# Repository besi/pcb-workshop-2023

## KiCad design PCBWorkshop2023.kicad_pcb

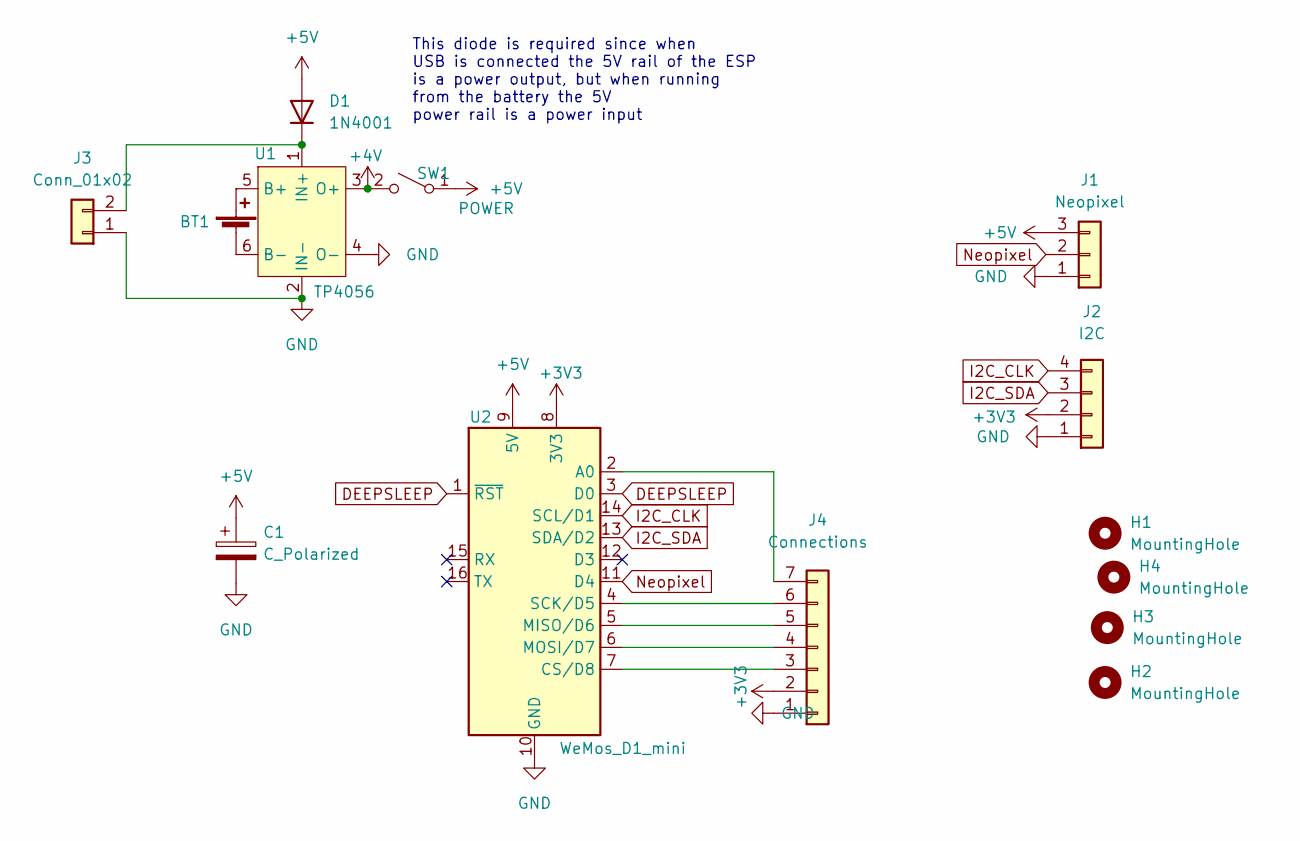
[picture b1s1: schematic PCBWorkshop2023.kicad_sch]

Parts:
BT1: Battery_Cell; JST_EH_S2B-EH_1x02_P2.50mm_Horizontal
C1: C_Polarized; C_Radial_D6.3mm_H11.0mm_P2.50mm
D1: 1N4001; D_A-405_P7.62mm_Horizontal
H1, H2, H3, H4: MountingHole; MountingHole_3.2mm_M3
J1: Neopixel; PinHeader_1x03_P2.54mm_Vertical
J2: I2C; PinHeader_1x04_P2.00mm_Vertical
J3: Conn_01x02; PinHeader_1x02_P2.54mm_Vertical
J4: Connections; PinHeader_1x07_P2.54mm_Vertical
SW1: POWER; SW_Push_1P2T_Vertical_E-Switch_800UDP8P1A1M6
U1: TP4056
U2: WeMos_D1_mini; WEMOS_D1_mini_light

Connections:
+3V3: J2.2, J4.2, U2.8 (3V3)
+4V: SW1.2 (B), U1.3 (O+)
+5V: C1.1, D1.2 (A), J1.3, SW1.1 (A), U2.9 (5V)
DEEPSLEEP: U2.1 (~RST), U2.3 (D0)
GND: C1.2, J1.1, J2.1, J3.1, J4.1, U1.2 (IN-), U1.4 (O-), U2.10 (GND)
I2C_CLK: J2.4, U2.14 (SCL/D1)
I2C_SDA: J2.3, U2.13 (SDA/D2)
Neopixel: J1.2, U2.11 (D4)
unnamed: BT1.1 (+), U1.5 (B+)
unnamed: BT1.2 (-), U1.6 (B-)
unnamed: D1.1 (K), J3.2, U1.1 (IN+)
unnamed: J4.3, U2.7 (CS/D8)
unnamed: J4.4, U2.6 (MOSI/D7)
unnamed: J4.5, U2.5 (MISO/D6)
unnamed: J4.6, U2.4 (SCK/D5)
unnamed: J4.7, U2.2 (A0)

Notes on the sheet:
This diode is required since when USB is connected the 5V rail of the ESP is a power output, but when running from the battery the 5V power rail is a power input

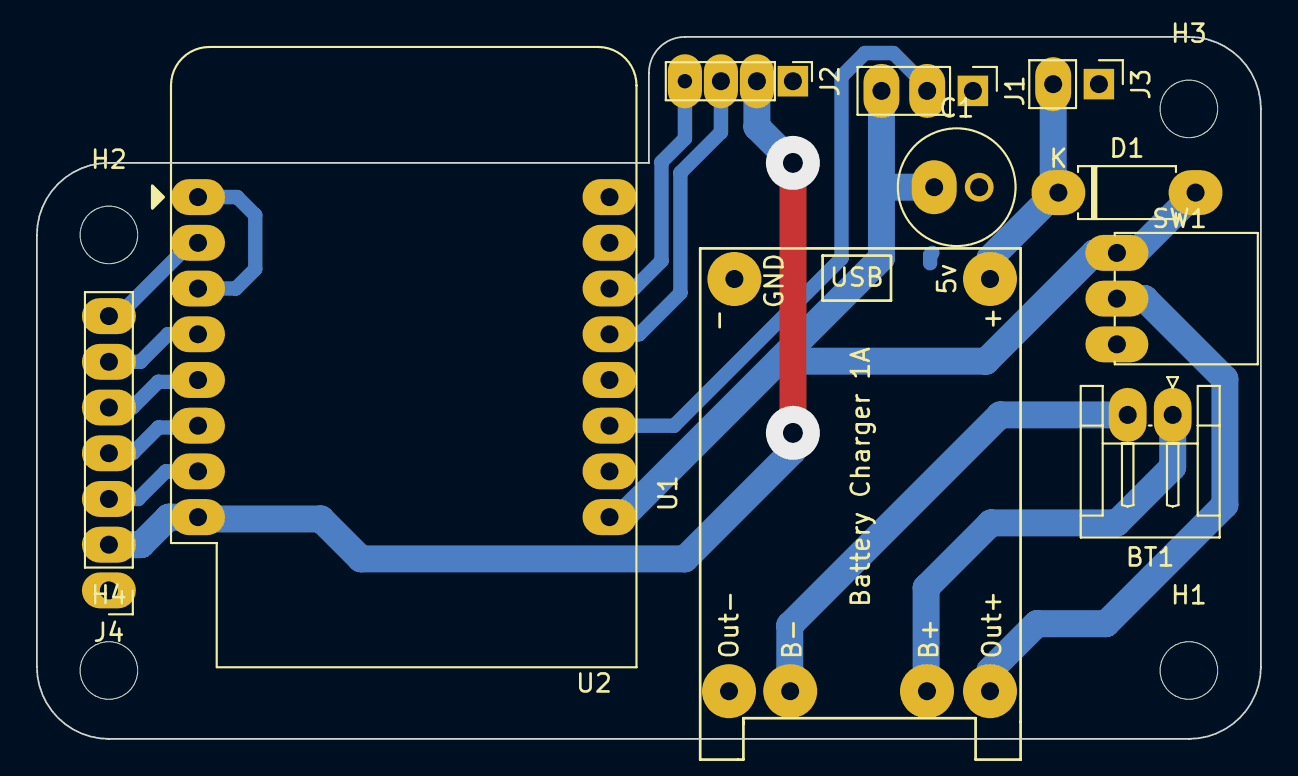
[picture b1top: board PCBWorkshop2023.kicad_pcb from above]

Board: 2 copper layers, 68.0 x 39.0 mm, 14 parts (0 on the bottom side), 16 nets.

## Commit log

2023-02-22 Empty project with rp4056 module
2023-02-22 Initial design and PCB
2023-02-22 Initial Routing
2023-02-23 Changes with Bernd
2023-02-23 Rounded corners and switch
2023-02-24 Prepare for milling
2023-02-24 Improvements
